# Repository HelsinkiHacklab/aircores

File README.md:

# Air Core gauges

3D models for coilforms, code and circuit designs for driving them

Here's a video of the first prototype in action: [normal speed][1] and [420fps][2]

[1]: http://www.youtube.com/watch?v=vhqzZveLjwU
[2]: http://www.youtube.com/watch?v=AHGWKIlYg_o

## spooler

3D parts for building a machine for winding air-core coils

## coilforms

3D printable coilforms, remember to put the rotor inside. (there will be more details to follow)

## driver

Arduino code to generate PWM to drive the aircores, I2C controlled.

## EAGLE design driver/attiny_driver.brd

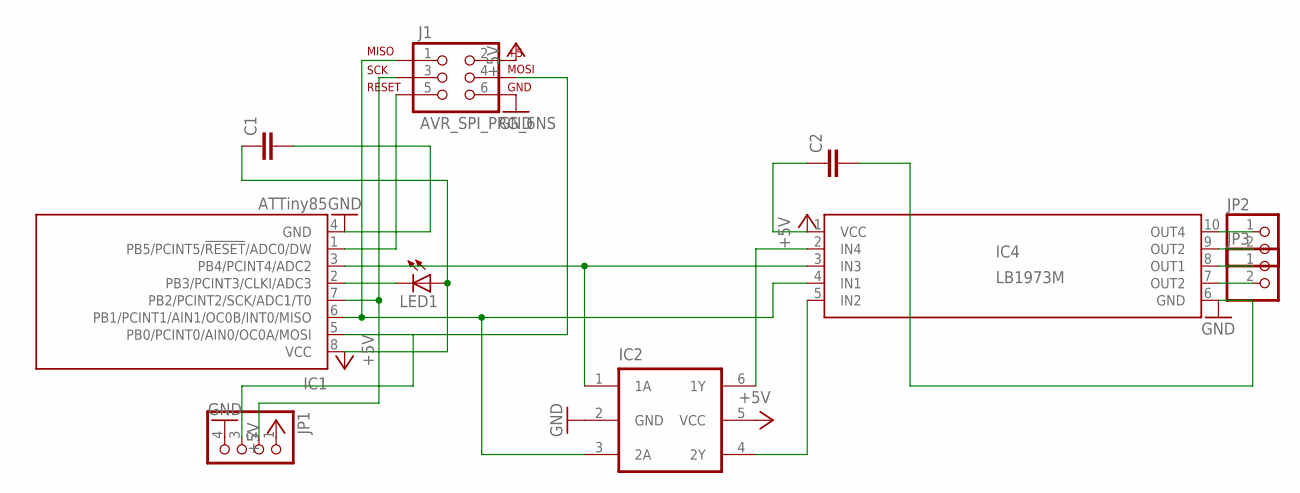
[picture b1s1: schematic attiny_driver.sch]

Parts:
C1, C2: C-EUC0805; C0805
IC1: ATTiny85; 8S2
IC2: IC_BUFF_SN74LVC2G17DBV; DBV-R-PDSO-G6
IC4: LB1973M; SSOP10
J1: AVR_SPI_PRG_6NS; 2X3-NS
JP1: PINHD-1X4; 1X04
JP2, JP3: PINHD-1X2; 1X02
LED1: LED0603; LED-0603

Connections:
+5V: C1.1, C2.1, IC1.8 (VCC), IC2.5 (VCC), IC4.1 (VCC), J1.2, JP1.1, LED1.A
GND: C1.2, C2.2, IC1.4 (GND), IC2.2 (GND), IC4.6 (GND), J1.6, JP1.4
IN1/MISO: IC1.6 (PB1/PCINT1/AIN1/OC0B/INT0/MISO), IC2.3 (2A), IC4.4 (IN1), J1.1
IN2: IC2.4 (2Y), IC4.5 (IN2)
IN3: IC1.3 (PB4/PCINT4/ADC2), IC2.1 (1A), IC4.3 (IN3)
IN4: IC2.6 (1Y), IC4.2 (IN4)
unnamed: IC1.2 (PB3/PCINT3/CLKI/ADC3), LED1.C
unnamed: IC1.1 (PB5/PCINT5/!RESET!/ADC0/DW), J1.5
OUT1: IC4.8 (OUT1), JP3.1
OUT2: IC4.7 (OUT2), JP3.2
OUT3: IC4.9 (OUT2), JP2.2
OUT4: IC4.10 (OUT4), JP2.1
SCL/SCK: IC1.7 (PB2/PCINT2/SCK/ADC1/T0), J1.3, JP1.2
SDA/MOSI: IC1.5 (PB0/PCINT0/AIN0/OC0A/MOSI), J1.4, JP1.3

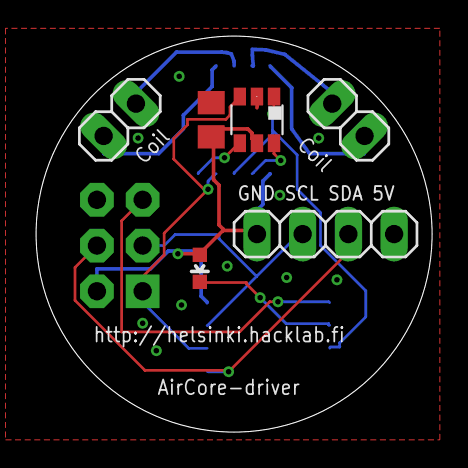
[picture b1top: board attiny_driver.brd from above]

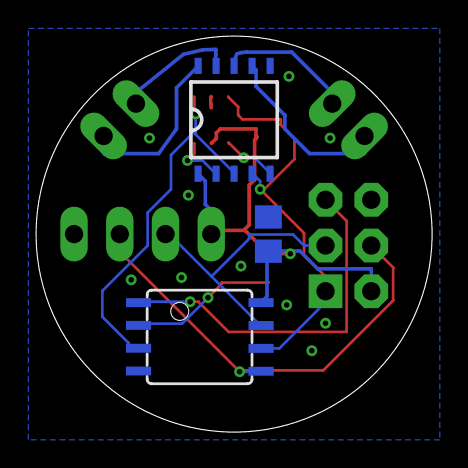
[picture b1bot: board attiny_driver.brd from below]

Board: 2 copper layers, 22.0 x 22.0 mm, 10 parts (3 on the bottom side), 14 nets.

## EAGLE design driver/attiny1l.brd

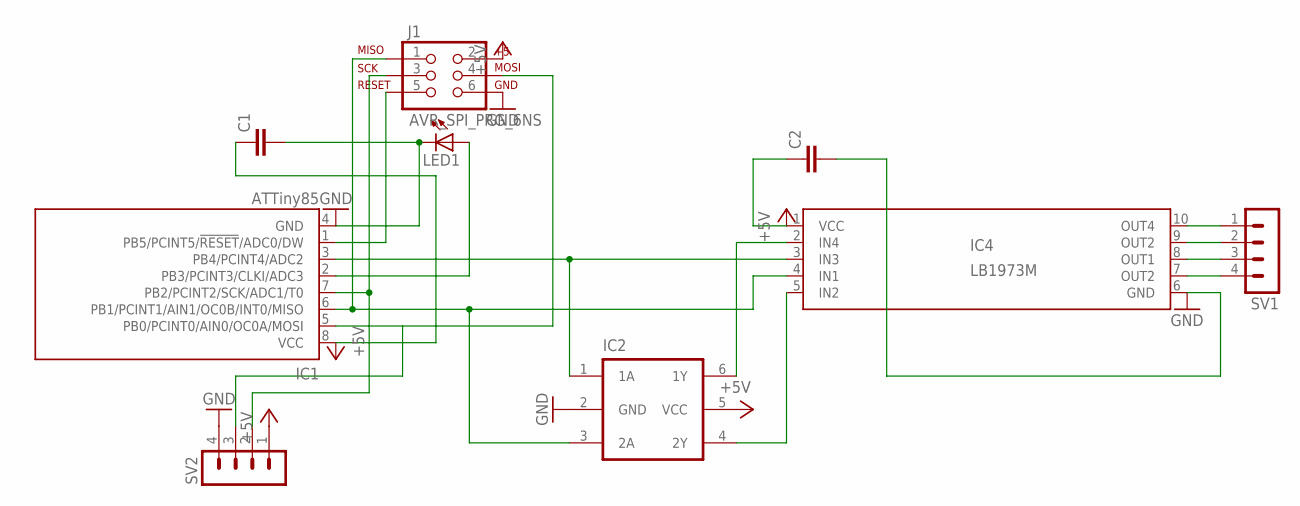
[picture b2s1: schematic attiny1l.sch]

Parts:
C1, C2: C-EUC0805; C0805
IC1: ATTiny85; 8S2
IC2: IC_BUFF_SN74LVC2G17DBV; DBV-R-PDSO-G6
IC4: LB1973M; SSOP10
J1: AVR_SPI_PRG_6NS; 2X3-NS
LED1: LED0603; LED-0603
SV1, SV2: MA04-1

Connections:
+5V: C1.1, C2.1, IC1.8 (VCC), IC2.5 (VCC), IC4.1 (VCC), J1.2, SV2.1
GND: C1.2, C2.2, IC1.4 (GND), IC2.2 (GND), IC4.6 (GND), J1.6, LED1.C, SV2.4
IN1/MISO: IC1.6 (PB1/PCINT1/AIN1/OC0B/INT0/MISO), IC2.3 (2A), IC4.4 (IN1), J1.1
IN2: IC2.4 (2Y), IC4.5 (IN2)
unnamed: IC1.3 (PB4/PCINT4/ADC2), IC2.1 (1A), IC4.3 (IN3)
unnamed: IC2.6 (1Y), IC4.2 (IN4)
unnamed: IC1.2 (PB3/PCINT3/CLKI/ADC3), LED1.A
unnamed: IC1.1 (PB5/PCINT5/!RESET!/ADC0/DW), J1.5
OUT1: IC4.8 (OUT1), SV1.3
OUT2: IC4.7 (OUT2), SV1.4
OUT3: IC4.9 (OUT2), SV1.2
OUT4: IC4.10 (OUT4), SV1.1
SCL/SCK: IC1.7 (PB2/PCINT2/SCK/ADC1/T0), J1.3, SV2.2
SDA/MOSI: IC1.5 (PB0/PCINT0/AIN0/OC0A/MOSI), J1.4, SV2.3

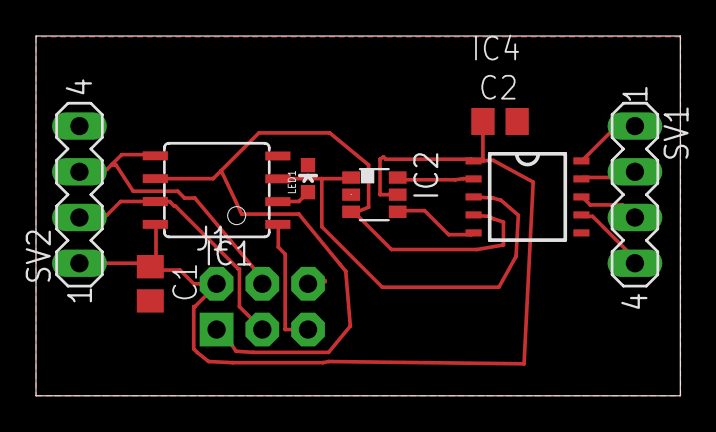
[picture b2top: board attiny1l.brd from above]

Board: 1 copper layer, 35.8 x 20.0 mm, 9 parts (0 on the bottom side), 14 nets.

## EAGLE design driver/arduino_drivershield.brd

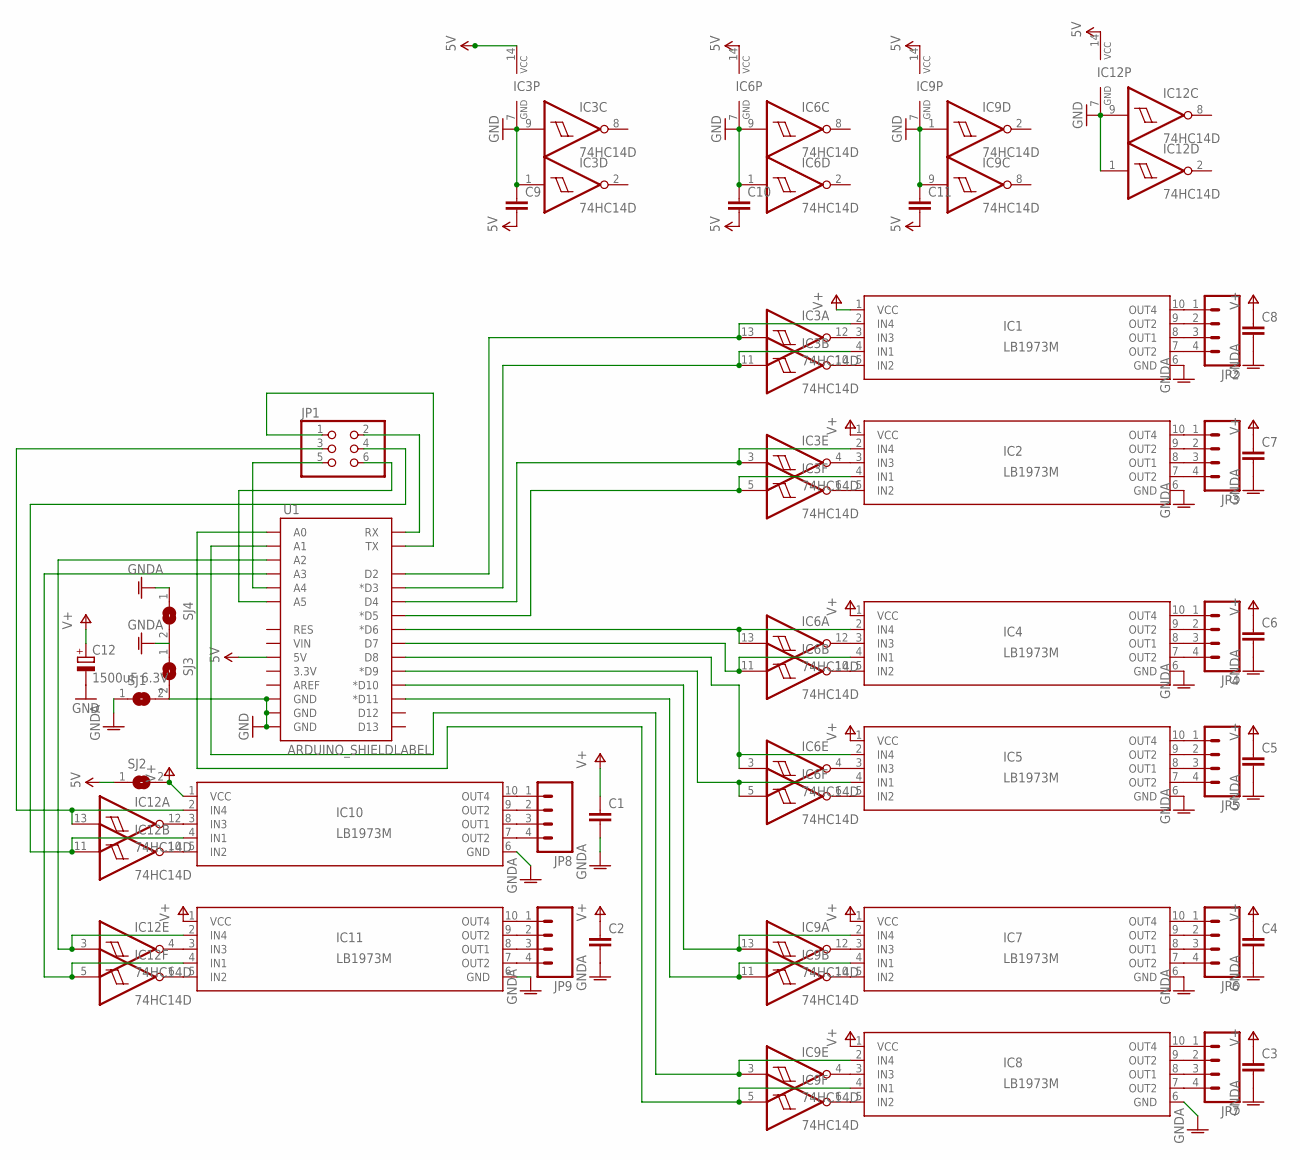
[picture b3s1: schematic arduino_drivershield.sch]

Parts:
C1, C2, C3, C4, C5, C6, C7, C8, C9, C10, C11: C-EUC0805; C0805
C12: 1500uF 6.3V; E5-10,5
IC1, IC2, IC4, IC5, IC7, IC8, IC10, IC11: LB1973M; SSOP10
IC3, IC6, IC9, IC12: 74HC14D; SO14
JP1: PINHD-2X3; 2X03
JP2, JP3, JP4, JP5, JP6, JP7, JP8, JP9: M041X04_NO_SILK; 1X04_NO_SILK
SJ1, SJ2, SJ3, SJ4: SJ
U1: ARDUINO_SHIELDLABEL; DUEMILANOVE_SHIELD

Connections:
5V: C9.2, C10.2, C11.2, IC3.14 (VCC), IC6.14 (VCC), IC9.14 (VCC), IC12.14 (VCC), SJ2.1, U1.5V
GND: C9.1, C10.1, C11.1, C12.-, IC3.1 (I), IC3.7 (GND), IC3.9 (I), IC6.1 (I), IC6.7 (GND), IC6.9 (I), IC9.1 (I), IC9.7 (GND), IC9.9 (I), IC12.1 (I), IC12.7 (GND), IC12.9 (I), SJ1.2, U1.GND@0 (GND), U1.GND@1 (GND), U1.GND@2 (GND)
GND@PWR: C1.2, C2.2, C3.2, C4.2, C5.2, C6.2, C7.2, C8.2, IC1.6 (GND), IC2.6 (GND), IC4.6 (GND), IC5.6 (GND), IC7.6 (GND), IC8.6 (GND), IC10.6 (GND), IC11.6 (GND), SJ1.1, SJ3.1, SJ4.1
unnamed: IC1.7 (OUT2), JP2.4
unnamed: IC1.8 (OUT1), JP2.3
unnamed: IC1.9 (OUT2), JP2.2
unnamed: IC1.10 (OUT4), JP2.1
unnamed: IC2.7 (OUT2), JP3.4
unnamed: IC2.8 (OUT1), JP3.3
unnamed: IC2.9 (OUT2), JP3.2
unnamed: IC2.10 (OUT4), JP3.1
unnamed: IC1.3 (IN3), IC3.12 (O)
unnamed: IC1.5 (IN2), IC3.10 (O)
unnamed: IC2.3 (IN3), IC3.4 (O)
unnamed: IC2.5 (IN2), IC3.6 (O)
unnamed: IC1.4 (IN1), IC3.11 (I), U1.D3 (*D3)
unnamed: IC1.2 (IN4), IC3.13 (I), U1.D2
unnamed: IC2.2 (IN4), IC3.3 (I), U1.D4
unnamed: IC2.4 (IN1), IC3.5 (I), U1.D5 (*D5)
unnamed: IC4.7 (OUT2), JP4.4
unnamed: IC4.8 (OUT1), JP4.3
unnamed: IC4.9 (OUT2), JP4.2
unnamed: IC4.10 (OUT4), JP4.1
unnamed: IC5.7 (OUT2), JP5.4
unnamed: IC5.8 (OUT1), JP5.3
unnamed: IC5.9 (OUT2), JP5.2
unnamed: IC5.10 (OUT4), JP5.1
unnamed: IC4.3 (IN3), IC6.12 (O)
unnamed: IC4.5 (IN2), IC6.10 (O)
unnamed: IC10.2 (IN4), IC12.13 (I), JP1.3
unnamed: IC8.2 (IN4), IC9.3 (I), U1.A1
unnamed: IC10.4 (IN1), IC12.11 (I), JP1.4
unnamed: IC11.2 (IN4), IC12.3 (I), U1.A2
unnamed: IC4.4 (IN1), IC6.11 (I), U1.D7
unnamed: IC4.2 (IN4), IC6.13 (I), U1.D6 (*D6)
unnamed: IC5.2 (IN4), IC6.3 (I), U1.D8
unnamed: IC5.4 (IN1), IC6.5 (I), U1.D9 (*D9)
unnamed: IC5.3 (IN3), IC6.4 (O)
unnamed: IC5.5 (IN2), IC6.6 (O)
unnamed: IC7.7 (OUT2), JP6.4
unnamed: IC7.8 (OUT1), JP6.3
unnamed: IC7.9 (OUT2), JP6.2
unnamed: IC7.10 (OUT4), JP6.1
unnamed: IC8.7 (OUT2), JP7.4
unnamed: IC8.8 (OUT1), JP7.3
unnamed: IC8.9 (OUT2), JP7.2
unnamed: IC8.10 (OUT4), JP7.1
unnamed: IC7.3 (IN3), IC9.12 (O)
unnamed: IC7.5 (IN2), IC9.10 (O)
unnamed: IC7.4 (IN1), IC9.11 (I), U1.D11 (*D11)
unnamed: IC7.2 (IN4), IC9.13 (I), U1.D10 (*D10)
unnamed: IC8.4 (IN1), IC9.5 (I), U1.A0
unnamed: IC8.3 (IN3), IC9.4 (O)
unnamed: IC8.5 (IN2), IC9.6 (O)
unnamed: IC10.7 (OUT2), JP8.4
unnamed: IC10.8 (OUT1), JP8.3
unnamed: IC10.9 (OUT2), JP8.2
unnamed: IC10.10 (OUT4), JP8.1
unnamed: IC11.7 (OUT2), JP9.4
unnamed: IC11.8 (OUT1), JP9.3
unnamed: IC11.9 (OUT2), JP9.2
unnamed: IC11.10 (OUT4), JP9.1
unnamed: IC10.3 (IN3), IC12.12 (O)
unnamed: IC10.5 (IN2), IC12.10 (O)
unnamed: IC11.4 (IN1), IC12.5 (I), U1.A3
unnamed: IC11.3 (IN3), IC12.4 (O)
unnamed: IC11.5 (IN2), IC12.6 (O)
RX: JP1.2, U1.RX
SCL: JP1.6, U1.A5
SDA: JP1.5, U1.A4
TX: JP1.1, U1.TX
V+: C1.1, C2.1, C3.1, C4.1, C5.1, C6.1, C7.1, C8.1, C12.+, IC1.1 (VCC), IC2.1 (VCC), IC4.1 (VCC), IC5.1 (VCC), IC7.1 (VCC), IC8.1 (VCC), IC10.1 (VCC), IC11.1 (VCC), SJ2.2

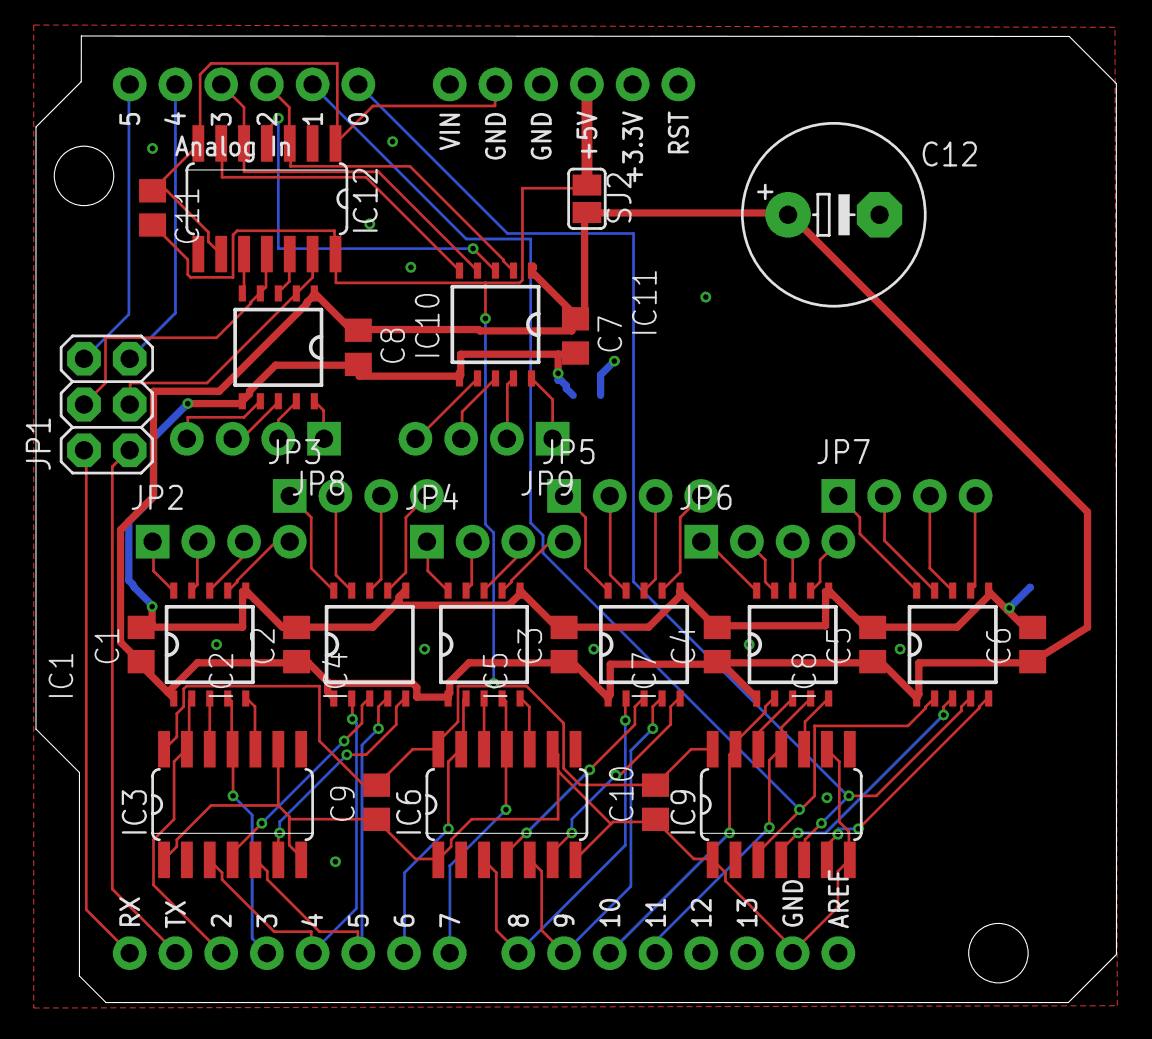
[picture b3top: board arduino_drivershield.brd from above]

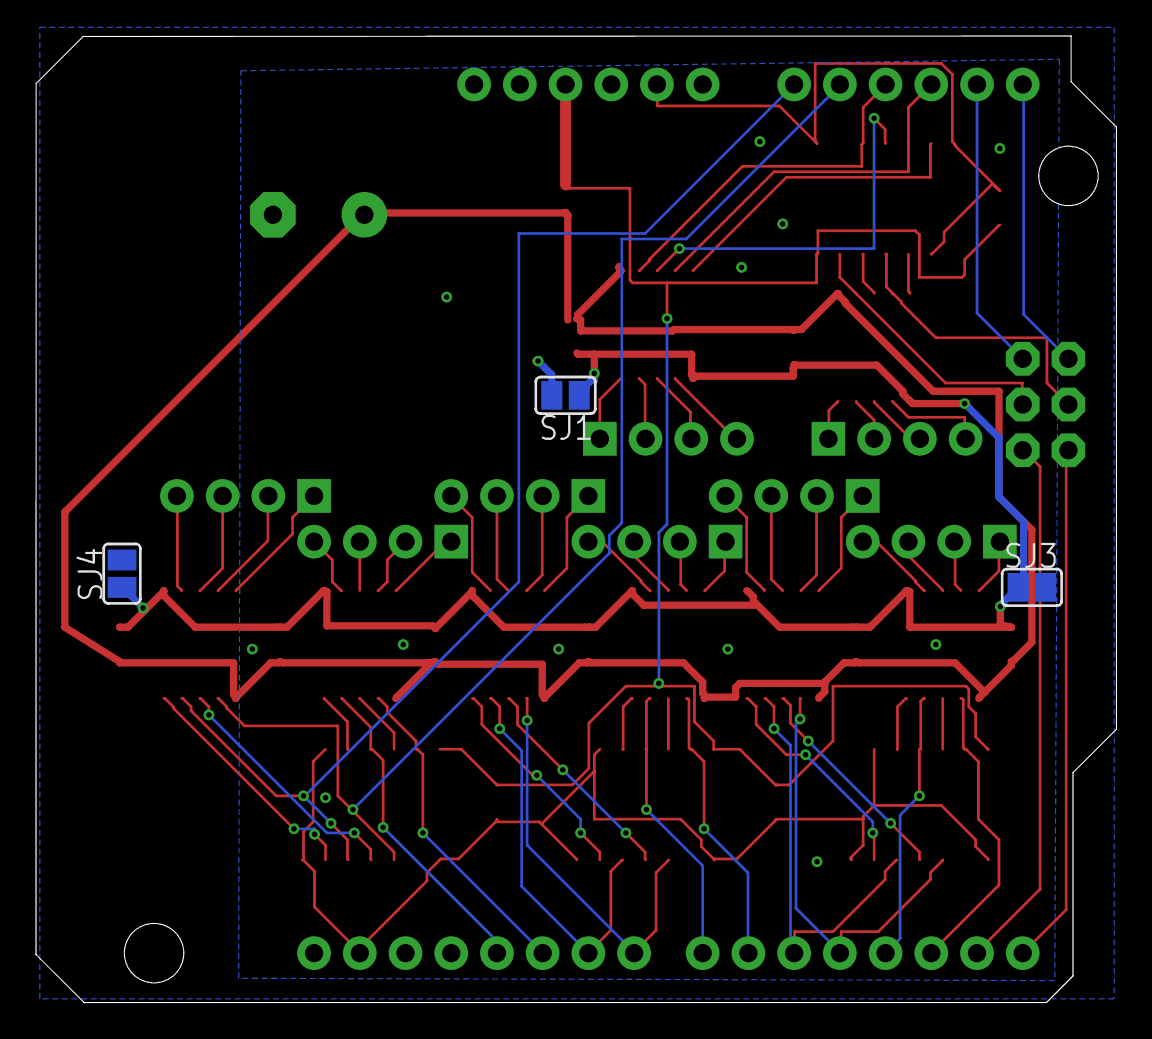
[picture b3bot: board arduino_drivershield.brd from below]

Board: 2 copper layers, 60.0 x 53.7 mm, 38 parts (3 on the bottom side), 72 nets.

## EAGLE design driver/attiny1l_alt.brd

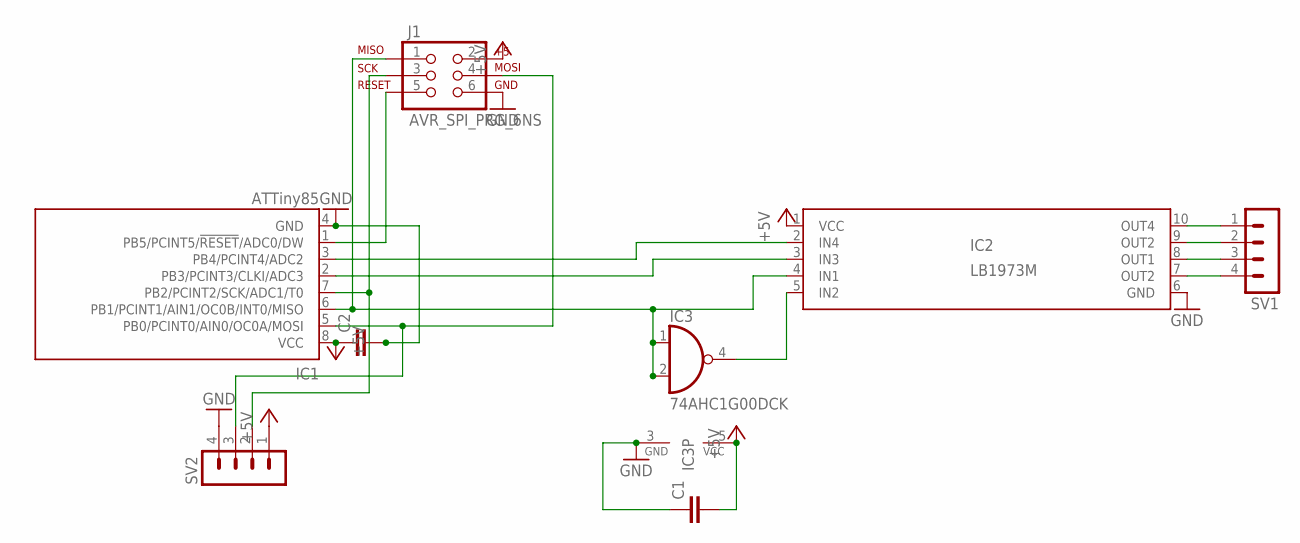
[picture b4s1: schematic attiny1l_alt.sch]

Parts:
C1, C2: C-EUC0805; C0805
IC1: ATTiny85; 8S2
IC2: LB1973M; SSOP10
IC3: 74AHC1G00DCK; SC70-5
J1: AVR_SPI_PRG_6NS; 2X3-NS
SV1, SV2: MA04-1

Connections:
+5V: C1.2, C2.1, IC1.8 (VCC), IC2.1 (VCC), IC3.5 (VCC), J1.2, SV2.1
GND: C1.1, C2.2, IC1.4 (GND), IC2.6 (GND), IC3.3 (GND), J1.6, SV2.4
IN1/MISO: IC1.6 (PB1/PCINT1/AIN1/OC0B/INT0/MISO), IC2.4 (IN1), IC3.1 (I0), IC3.2 (I1), J1.1
IN2: IC2.5 (IN2), IC3.4 (O)
IN3: IC1.2 (PB3/PCINT3/CLKI/ADC3), IC2.3 (IN3)
IN4: IC1.3 (PB4/PCINT4/ADC2), IC2.2 (IN4)
OUT1: IC2.8 (OUT1), SV1.3
OUT2: IC2.7 (OUT2), SV1.4
OUT3: IC2.9 (OUT2), SV1.2
OUT4: IC2.10 (OUT4), SV1.1
RESET-: IC1.1 (PB5/PCINT5/!RESET!/ADC0/DW), J1.5
SCL/SCK: IC1.7 (PB2/PCINT2/SCK/ADC1/T0), J1.3, SV2.2
SDA/MOSI: IC1.5 (PB0/PCINT0/AIN0/OC0A/MOSI), J1.4, SV2.3

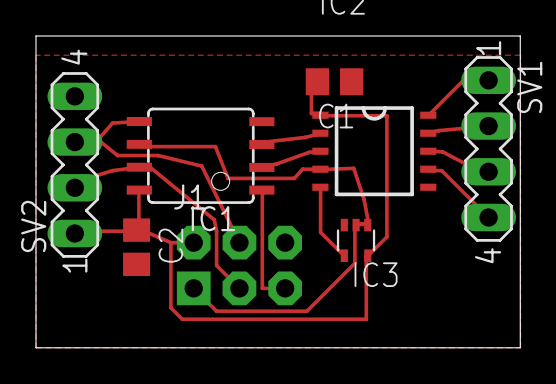
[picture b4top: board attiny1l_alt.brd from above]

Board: 1 copper layer, 26.9 x 17.3 mm, 8 parts (0 on the bottom side), 13 nets.

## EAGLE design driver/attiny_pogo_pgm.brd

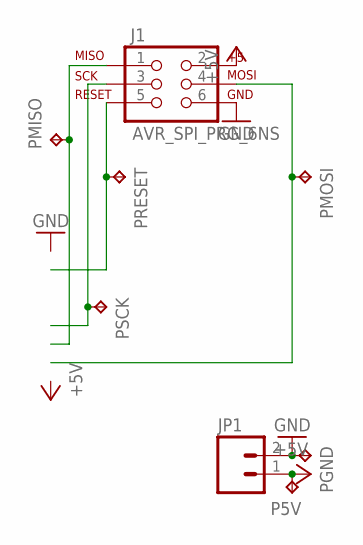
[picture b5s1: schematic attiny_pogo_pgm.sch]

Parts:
J1: AVR_SPI_PRG_6NS; 2X3-NS
JP1: M02PTH; 1X02
P5V: TPTP10R; TP10R
PGND: TPTP10R; TP10R
PMISO: TPTP10R; TP10R
PMOSI: TPTP10R; TP10R
PRESET: TPTP10R; TP10R
PSCK: TPTP10R; TP10R

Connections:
+5V: J1.2, JP1.1, P5V.TP
GND: J1.6, JP1.2, PGND.TP
IN1/MISO: J1.1, PMISO.TP
RESET-: J1.5, PRESET.TP
SCL/SCK: J1.3, PSCK.TP
SDA/MOSI: J1.4, PMOSI.TP

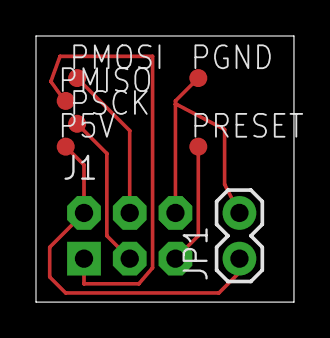
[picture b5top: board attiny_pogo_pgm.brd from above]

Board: 1 copper layer, 14.3 x 14.8 mm, 8 parts (0 on the bottom side), 6 nets.

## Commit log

2012-05-01 90deg angles for the tube-axes
2012-05-01 the gears from my laptop
2012-05-01 this actually was not supposed to be here
2012-05-01 version that should print better
2012-05-01 and exported STL of 91a8606
2012-05-01 noticed this fails when sleeve size is changed, need to look into that later
2012-05-01 oops, forgot to divide by two, it still does not quite work as parametric but again that will need to wait untill later
2012-05-01 and remember to turn it back sideways
2012-05-01 oops missed an union there
2012-05-01 trying another approach to lessen overhang and movement accuracy issues
2012-05-08 minor reorg
2012-05-12 Suovulas soft-PWM driving code
2012-05-12 coilforms by suovula, work surprisingly well
2012-05-12 I2C control of the positions
2012-05-12 enhanced readme
2012-05-12 suovula adjusted values to reduce skipping
2012-05-15 Suovula should fill in the gaps here
2012-05-16 started making protoboard for ATTiny based I2C controlled driver board
2012-05-16 gates for splitting the PWM signals so we can live with two PWM outputs instead of 4
2012-05-17 made a part for the h-bridge used
2012-05-17 the schematic should be ok now, had to sacrificy one HW PWM for the I2C but we should have plenty of cycles to do it in software if neccessary
2012-05-17 very initial placement
2012-05-17 trying to find got placement
2012-05-17 it seems the autogenerated package lacked SMD pads in footprint, lets try this again...
2012-05-17 this generated package looks better
2012-05-17 let us try this again...
2012-05-17 basic autorouter and drc configs for 1-layer board
2012-05-17 1L routing done, some airwires will be needed but that is to be expected
2012-05-17 rotating the attiny gave better results
2012-05-17 I guess I forgot to save...
2012-05-17 netlist for the H-bridge
2012-05-17 adjust dimension
2012-05-17 adjust routing for easier soldering withoud soldermask
2012-05-17 it seems this still works with 8mil trace width
2012-05-17 the attiny has already complement output we can use to drive the other coil
2012-05-17 routed
2012-05-17 routing adjustments
2012-05-17 started making test code for ATTiny based I2C controlled PWM driver
2012-05-17 correct net name
2012-05-17 rotating the NAND gate gave a nicer way to handle the jumper wires we need
2012-05-17 smaller dimensions
2012-05-17 larger isolate for the copper pour to make soldering the H-bridge without soldermask easier
2012-05-17 I2C setting of the HW-PWM works, but the lib is somehow funky it acknowledges every address after the slave address...
2012-05-17 this way SW pulsing works, I get output, it seems the NAND gate wired as not has some sort of contact problem since I only see one side the of HW-PWM signal
2012-05-17 added link to source of the TinyWireS -library
2012-05-23 started designing arduino shield for driving 8 cores with the LB1973M H-bridges (and 7414s to provide the complement drive signals)
2012-05-23 2x4 connectors for the coils
2012-05-23 wire the logic pins, this is all very initial the whole placement needs to be redone and some pins may need to be shuffled around
2012-05-23 board dimensions and ground-plane
2012-06-05 it seems I had two checkouts, this is a change from the other one...
2012-06-05 making a pogo-pin programmer for SMD attiny boards, new the attiny is still overlaid so I can tune placement of the pins
2012-06-05 prepare for routing
2012-06-05 use slightly bigger pads for the pogo pins
2012-06-06 the footpring was actually a bit too wide, made it 20mils narrower
2012-06-06 very quick and dirty reorg for new footprint
2012-06-06 replace the H-bridges with the updated one
2012-06-07 Suovulas notes about pins and timers
2012-06-07 clean up the copy-paste
2012-06-08 added links to the YT videos of the first proto
2012-06-09 adding placeholders for some features I think are usefull
2012-06-09 initialize the angle to known one on boot
2012-06-09 clarifyind comments
2012-06-09 trying to get the HW pwm working
2012-06-09 ORC1A works, B works haflway...
2012-06-09 the clear on match is not what we want, and general debugging
2012-06-09 for some reason having this value outside some range we got no output
2012-06-09 minor reorg and temp disable of the I2C receive handler and debug code to set the angle every second
2012-06-09 restore full speed pwm (lowered to see if the weird things on scope were maybe caused by scope aliasing), minor cleanup
2012-06-09 Suovulas Sine table for angle->pwm conversions
2012-06-09 fixes after reviewing with suovula
2012-06-09 debugging...
2012-06-09 comment explaining a weird value
2012-06-09 use correct mask
2012-06-09 the previous mask was correct afterall
2012-06-09 make sure ii is limited to 12bit
2012-06-09 test the smaller table, seems to work just fine -> our problems on the tiny board come from elsewhere
2012-06-09 remove all I2C stuff while debugging the actual driver
2012-06-09 added bypass caps, hopefully it helps with the weird clock/reset issues we are having
2012-06-09 adjust routing for easier home fabrication
2012-06-09 use dual NOT and added bypass caps
2012-06-09 QnD routed
2012-06-11 alternative placing from harald
2012-06-11 adjusted signals a bit, it seems adding one more 7414 will be prudent
2012-06-11 switched to SIL connectors for nicer schematic
2012-06-11 starting over...
2012-06-11 this seems to be a good way, two h-bridges to one 7414
2012-06-11 second group
2012-06-11 otoh tying the unused inputs to the gnd-plane is probably better idea
2012-06-11 signals routed, though pin13 might be verboten for output due to the led in that case need to replace 12,3 with analog0,1
2012-06-11 load fusion pcb service DRU
2012-06-11 leave pin 12 and 13 out, replace with a0 and a1
2012-06-11 it might be ugly but it is routed
2012-06-11 approve ERC warnings
2012-06-11 surprise, going to 6mils (I can still just handle that in my home lab) made this routable with one airwire in 1 layer...
2012-06-12 attempting to have higher power traces for the h-bridges alone (gnd is a bit tricky if I want to use the plane on the bottom for signal gnd as well
2012-06-12 testing routing
2012-06-12 bypass caps for all h-bridges
2012-06-12 the expiriment with the @signal names did not work out
2012-06-12 the formar was SIGNAL@num...
2012-06-12 but it seems it only works in IC definitions :(
2012-06-12 so back top bridging with wires...
2012-06-12 add caps for the inverters too
2012-06-12 autorouted
2012-06-12 seems I forgot to save the last routing
2012-06-12 adding a cap across the h-bridge seems to have solved our mysterious issues so will start re-enabling the I2C stuff
2012-06-12 use demo_mode variable to start rotating on boot but when first I2C position comes in, keep it
2012-06-12 remember to enable the I2C interface
2012-06-12 simplifying the handler made setting the position to work, but the tinywire lib still does something funky (ike hangs if I do an address scan...)
2012-06-12 after modification to the tinywireS (and fixing a off-by-one error...) it works
2012-06-12 we need a modified TinyWireS library
2012-06-12 remove obsolete code
2012-06-13 added some more jumper to hopefully get better ground connections
2012-06-13 thicker trace from 5V to power net v+, better placement for one jumper
2012-06-13 realized the GND jumpers should probably be at bottom side
2012-06-13 routed, the one airwire is no problem since the GND pins are connected on the arduino board
2012-06-13 tuning dimension to the shield outline
2012-06-13 dimension should be nicer now
2012-06-13 added top-layer GND polygon too
2012-06-13 remember the smaller grid for the future
2012-06-13 crap, there was still a leftover from myh signal namig adventures
2012-06-13 maybe now all my old follies are fixed?
2012-06-13 added via to get more ground coverage
2012-06-13 the bottom is now good
2012-06-13 a few more vias to get more copper under the h-bridges to move heat
2012-06-13 routed the v+ around as well so the "far side" ICs have shorter current path as well
2012-06-19 added one more low-ESR cap
2012-06-19 seems I messed up the net name here at some point, now corrected
2012-06-20 remove dead code
2012-06-20 added a debugging led
2012-06-20 otoh this way I can sample our input voltage when not driving the led...
2012-06-20 untested (but hey, it compiles :) code to store the configuration registers in EEPROM
2012-06-20 added an usefull link
2012-06-20 make EEPROM write triggered by explicit command (to avoid accidents)
2012-06-23 new software requires Re396837 of the board
2012-06-23 the alt board will no longer be supported
2012-06-23 maybe this prescaler setting is a bit better
2012-08-10 very simple breakout with ISP header in 1 layer for home-etching
2012-08-14 moving these files to another repo
2012-08-20 barely smoketested adaptation to the new and improved TinyWireS with even support (after a fashion...)
2012-08-25 started working on the actual I2C controller driver-board
2012-08-25 DRC loaded
2012-08-25 autorouter settings
2012-08-25 stopmask around the edges to allow grounding to the metal tube this and the aircore itself go into
2012-09-23 Totally new implementation for the software PWM generator.
2012-09-23 Keep the values of unused port pins. Not tested on real hardware.
2012-10-14 Phase corrected PWM
2012-10-14 Timer1 fixed
2012-10-14 slave should not enable pull-ups
2012-10-14 slaves should not use pull-ups
2012-10-17 Phase and Frequency Correct PWM mode. Gamma correction value for compensating AirCore nonlinearities, needs experimenting. Pin 13 can be used as oscilloscope trigger for PWM pulses
2012-10-17 Fixed pin mapping
2013-01-12 make work with new avr-gcc (and hopefully still allow it to work with old old
2013-09-24 detab
2013-10-01 make things smoother, and star reworking the wing design
2013-10-01 donut experiments
2013-10-01 make the edges rounded
2013-10-01 use the render statement to cache the wing module
2013-10-01 it seems the render statement led to memory leak
2013-10-01 use the prerendered wing
2013-10-01 exported new stl
2013-10-02 simple way to view the STL
2019-06-24 Flush the buffer at first sign of trouble

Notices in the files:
parts and their libraries:
SparkFun-Boards: Licensing: CC v3.0 Share-Alike You are welcome to use this library for commercial purposes.
